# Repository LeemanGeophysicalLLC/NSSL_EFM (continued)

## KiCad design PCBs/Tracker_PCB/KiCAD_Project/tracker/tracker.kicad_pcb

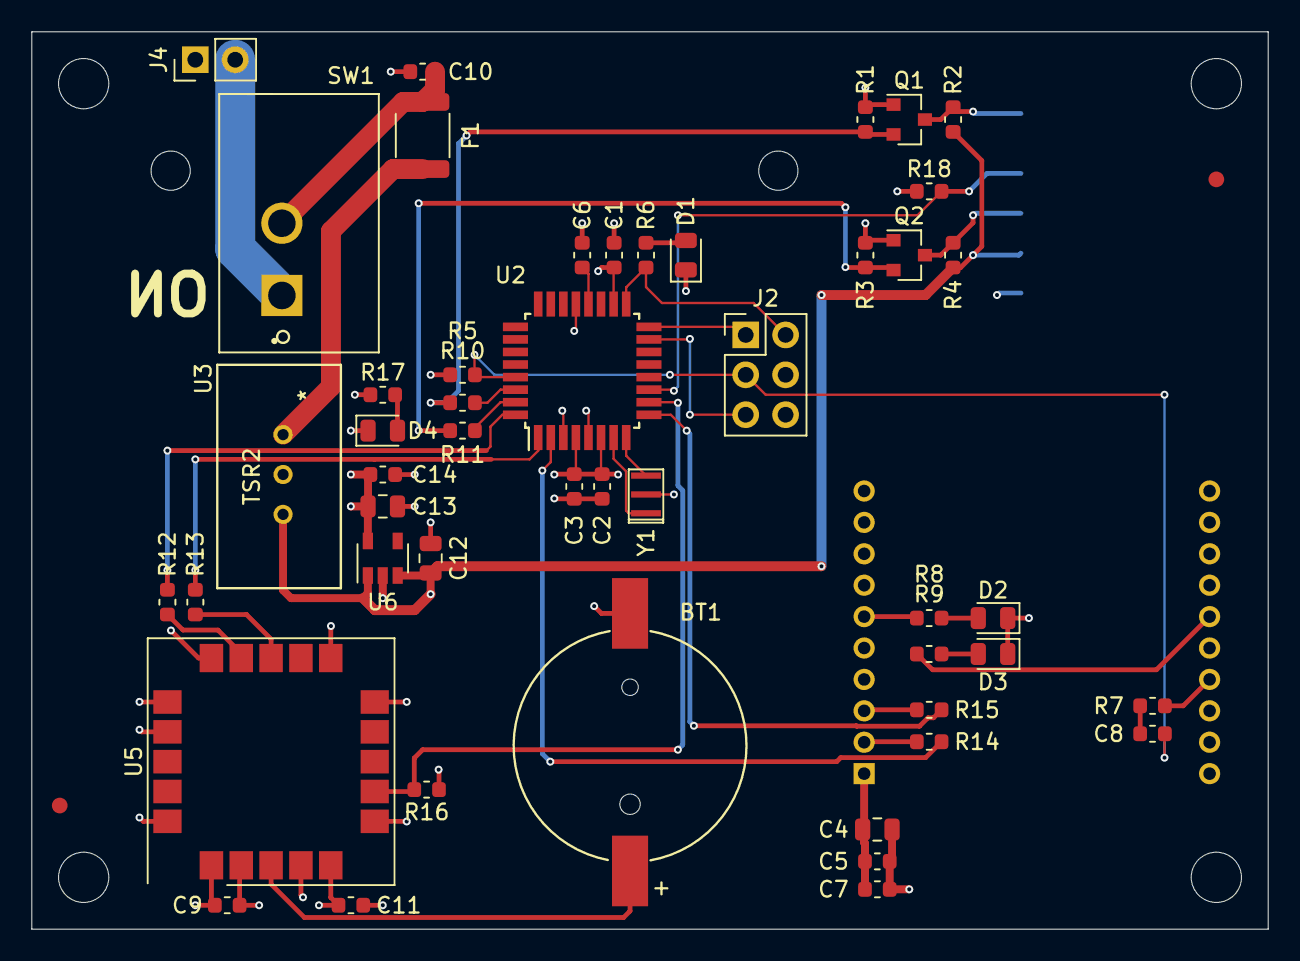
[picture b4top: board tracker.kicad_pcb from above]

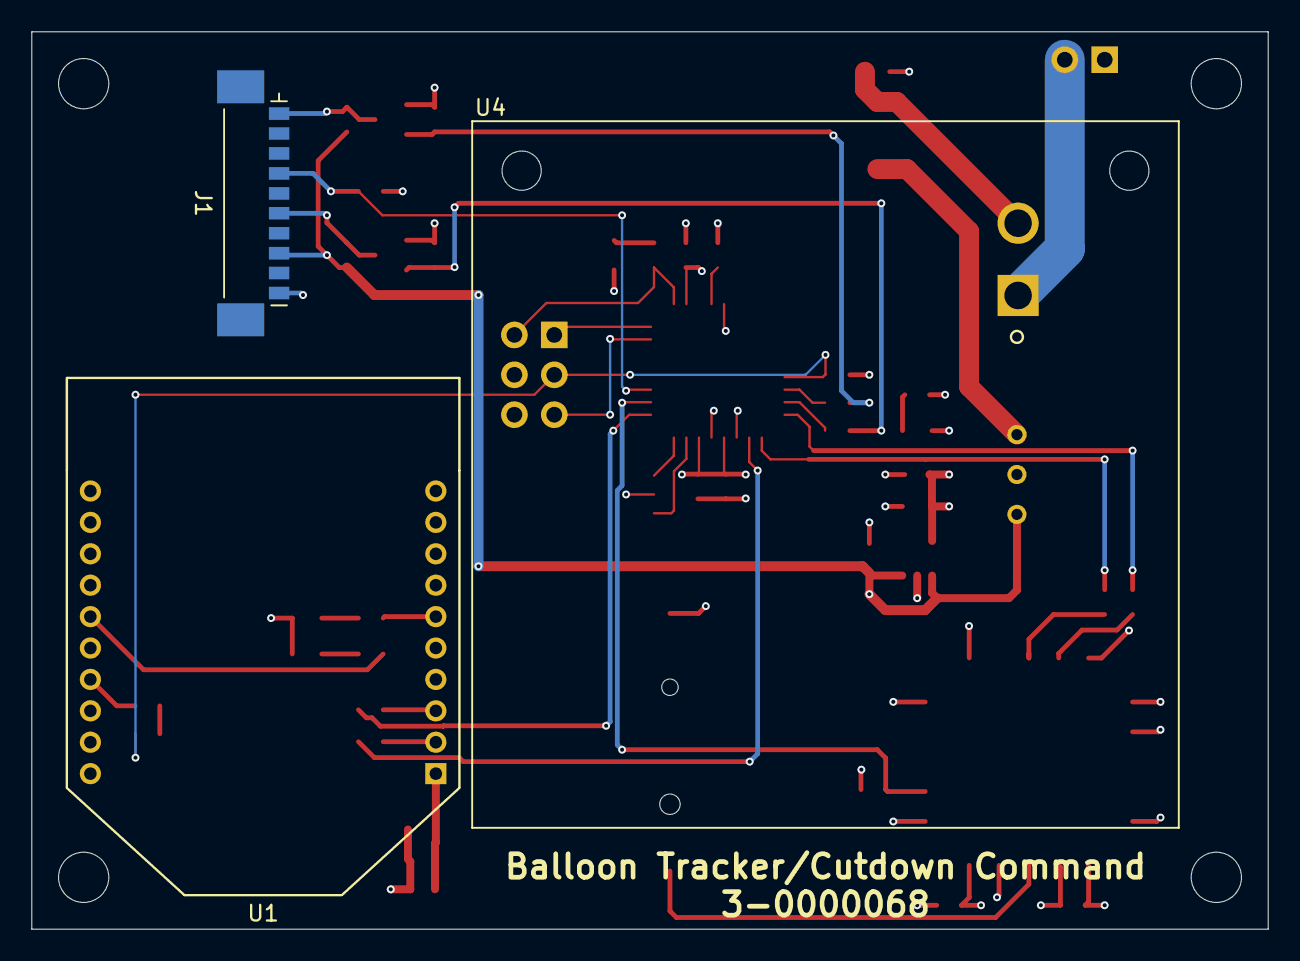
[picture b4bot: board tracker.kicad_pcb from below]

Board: 4 copper layers, 78.7 x 57.2 mm, 58 parts (3 on the bottom side), 38 nets.

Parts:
BT1: CR1220; S8411-45R
C1, C2, C3, C6, C7, C8, C9, C10, C11, C14: 1-0000007
C4, C12, C13: 1-0000075
C5: 1-0000018
D1, D2: Blue; LED_0805_2012Metric
D3: Yellow; LED_0805_2012Metric
D4: Green; LED_0805_2012Metric
F1: Polyfuse; Fuse_1812_4532Metric
FID1, FID2: Fiducial; Fiducial_1mm_Mask2mm
H1, H2, H3, H4: MountingHole; MountingHole_3.2mm_M3_DIN965
J1: RockBlock9603; picoblade
J2: ICSP; PinHeader_2x03_P2.54mm_Vertical
J4: Battery; PinHeader_1x02_P2.54mm_Vertical
PCB1: barepcb; BarePCB
Q1, Q2: BSS138; SOT-23
R1, R2, R3, R4: 1-0000013
R5, R16, R18: 1-0000010
R6, R8, R9, R17: 1-0000008
R7, R10, R11, R12, R13, R14, R15: 1-0000006
SW1: SW_SPST; SW_GF-123-0054
U1: XBee
U2: ATmega328P-AU; TQFP-32_7x7mm_P0.8mm
U3: TSR2; TSR 2-2450
U4: RockBlockMechanical; RockBlock_Mechanical
U5: ublox_SAM-M8Q
U6: MIC5219-3.3YM5; SOT-23-5
Y1: 16MHz; Resonator

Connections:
+3V3: C1.1, C2.1, C3.1, C4.1, C5.1, C7.1, C9.1, C11.1, C13.1, C14.1, J2.6, Q1.1, Q2.1, R1.1, R3.1, R5.1, R16.1, R17.1, R18.1, U1.1, U2.4, U2.6, U2.18, U5.2, U5.17, U6.5
GPS_PPS: R16.2, U2.10, U5.7
GPS_RX: R12.1, U5.14
GPS_TX: R13.1, U5.13
MISO: J2.1, U2.16
MOSI: J2.5, U2.15
unnamed: BT1.1, U5.3
unnamed: C6.1, U2.20
unnamed: C8.2, R7.1
unnamed: C10.1, F1.2, SW1.2
unnamed: D1.2, R6.2
unnamed: D2.2, R8.2
unnamed: D3.2, R9.2
unnamed: D4.2, R17.2
unnamed: F1.1, U3.1
unnamed: J4.2, SW1.1
unnamed: R7.2, U1.17
unnamed: R8.1, U1.6
unnamed: R9.1, U1.15
unnamed: R10.2, U2.30
unnamed: R11.2, U2.31
unnamed: R12.2, U2.32
unnamed: R13.2, U2.1
unnamed: R14.2, U2.2
unnamed: R15.2, U2.9
unnamed: U2.7, Y1.1
unnamed: U2.8, Y1.3
RB_5V: C12.1, J1.8, R2.1, R4.1, U3.3, U6.1, U6.3
RB_GND: BT1.2, C1.2, C2.2, C3.2, C4.2, C5.2, C6.2, C7.2, C9.2, C10.2, C11.2, C12.2, C13.2, C14.2, D1.1, D2.1, D3.1, D4.1, J1.10, J2.4, J4.1, U1.10, U2.3, U2.5, U2.21, U3.2, U5.1, U5.4, U5.5, U5.6, U5.10, U5.11, U5.15, U5.16, U5.20, U6.2, Y1.2
RB_NetAv: J1.4, R18.2, U2.11
RB_RXI: J1.6, Q2.3, R4.2
RB_RXI_3V3: Q2.2, R3.2, R11.1
RB_TXO: J1.1, Q1.3, R2.2
RB_TXO_3V3: Q1.2, R1.2, R10.1
RESET: C8.1, J2.3, R5.2, U2.29
SCK: J2.2, R6.1, U2.17
XBee_from_Uc: R15.1, U1.3
XBee_to_Uc: R14.1, U1.2

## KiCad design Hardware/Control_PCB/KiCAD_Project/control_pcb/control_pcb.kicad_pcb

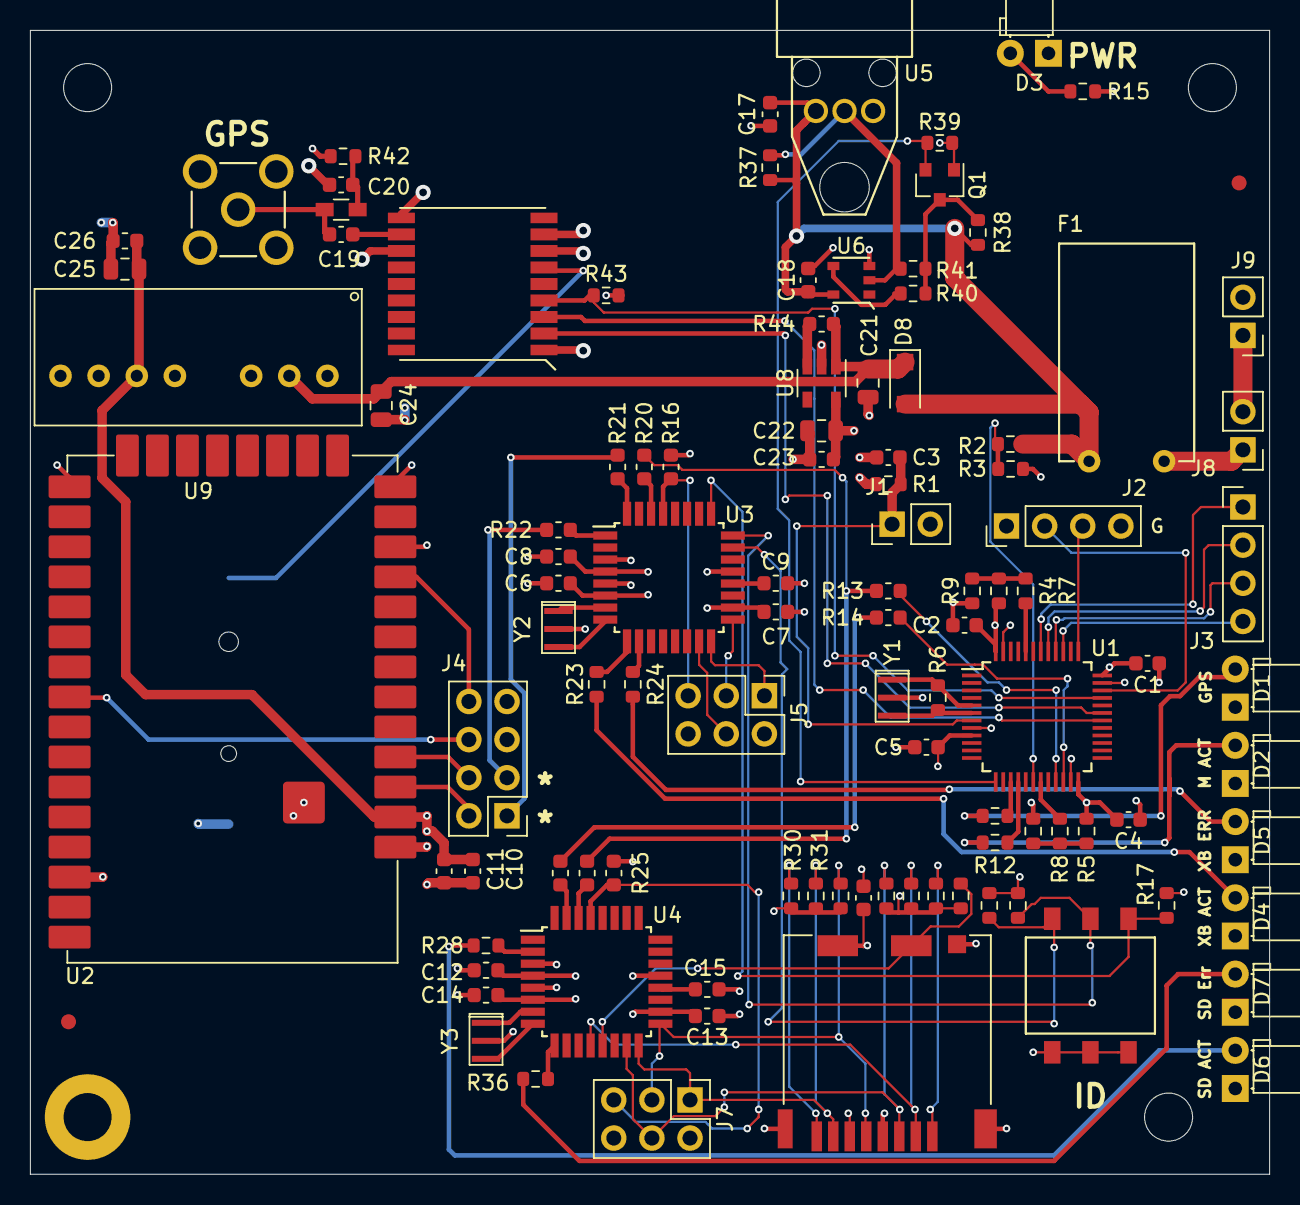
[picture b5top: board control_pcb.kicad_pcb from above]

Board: 4 copper layers, 82.6 x 76.2 mm, 112 parts (1 on the bottom side), 82 nets.

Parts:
AE1: Antenna_Shield; SMA
BT1: CR1220; S8411-45R
C1, C2, C4, C5, C16, C17, C18: 0.1u; C_0603_1608Metric
C3, C11: 1u; C_0603_1608Metric
C6, C7, C8, C9, C12, C13, C14, C15: 1-0000007
C10: 10u; C_0603_1608Metric
C19: 47pF; C_0603_1608Metric
C20: 10nF; C_0603_1608Metric
C21, C22, C24, C25: 1-0000075
C23, C26: 1-0000018
D1: GPS; LED_D3.0mm_Horizontal_O1.27mm_Z2.0mm_Clear
D2: ACT; LED_D3.0mm_Horizontal_O1.27mm_Z2.0mm_Clear
D3: Power; LED_D3.0mm_Horizontal_O1.27mm_Z2.0mm_Clear
D4, D6: Activity; LED_D3.0mm_Horizontal_O1.27mm_Z2.0mm_Clear
D5, D7: Error; LED_D3.0mm_Horizontal_O1.27mm_Z2.0mm_Clear
D8: D_Schottky; D_SOD-123F
F1: Polyfuse; RGEF250
FID1, FID2: Fiducial; Fiducial_1mm_Mask2mm
H1, H2, H3: MountingHole; MountingHole_3.2mm_M3_ISO7380
H4: MountingHole; MountingHole_3.2mm_M3_ISO7380_Pad
J1: Conn_01x02; Pin_Header_Straight_1x02_Pitch2.54mm
J2: ISP; Pin_Header_Straight_1x04_Pitch2.54mm
J3: Spare; Pin_Header_Straight_1x04_Pitch2.54mm
J4: XBee ISP; PinHeader_2x04_P2.54mm_Vertical
J5: XBee_uC_ISP; PinHeader_2x03_P2.54mm_Vertical
J6: Micro_SD_Card_Det; HRS_DM3CS-SF
J7: SD_uC_ISP; PinHeader_2x03_P2.54mm_Vertical
J8: External Switch; PinHeader_1x02_P2.54mm_Vertical
J9: Battery; PinHeader_1x02_P2.54mm_Vertical
L1: 27nH; R_0603_HandSoldering
PCB1: barepcb
Q1: BSS138; SOT-23
R1, R3, R17, R18, R19, R37, R38, R39: 10k; R_0603_1608Metric
R2: 18k; R_0603_1608Metric
R4, R5, R32, R41, R43: NP; R_0603_1608Metric
R6: 1M; R_0603_1608Metric
R7, R8, R29, R30, R31, R33, R34, R35: 100k; R_0603_1608Metric
R9, R10, R40: 0R0; R_0603_1608Metric
R11, R12, R15, R23, R24, R28, R36: 150; R_0603_1608Metric
R13, R14, R20, R21, R22, R26, R27: 1-0000006
R16, R25: 1-0000010
R42: 1-0000678; R_0603_1608Metric
R44: 1-0000174
SW1: ID Select; KAE03TGGR
U1: STM32F103CBT6; LQFP-48_7x7mm_Pitch0.5mm
U2: XTend
U3, U4: ATmega328P-AU; TQFP-32_7x7mm_P0.8mm
U5: IF-D96F
U6: TC4S584F; SOT753
U7: MAX-M8C; XCVR_MAX-M8C-0-10
U8: SPX3819M5-L-3-3; SOT-23-5
U9: 1-0000946
Y1, Y2, Y3: 8MHz; Resonator

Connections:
3V3_XBEE: C10.1, C11.1, C25.1, C26.1, U2.2, U9.6
+3V3: C1.2, C2.2, C4.2, C5.2, C6.1, C7.1, C8.1, C12.1, C13.1, C14.1, C16.2, C22.1, C23.1, J2.1, J5.2, J6.4, J7.2, Q1.1, R1.1, R4.2, R5.2, R15.2, R16.1, R17.1, R18.1, R19.1, R25.1, R29.1, R30.1, R31.1, R32.1, R33.1, R34.1, R35.1, R39.1, R42.1, R43.2, U1.9, U1.24, U1.36, U1.48, U3.4, U3.6, U3.18, U4.4, U4.6, U4.18, U7.7, U7.8, U8.5
+BATT: C17.1, C18.1, D8.2, F1.1, R2.1, R37.1, R38.1, U5.3, U6.5
/Boot0: R7.2, U1.44
/Boot1: R8.2, U1.19
/Reset: C3.1, J1.1, R1.2, U1.7
/SD/SD_uC_CD: J6.9, R29.2, U4.13
/SD/SD_uC_CS: J6.2, R34.2, U4.12
/SD/SD_uC_MISO: J6.7, J7.1, R31.2, U4.16
/SD/SD_uC_MOSI: J6.3, J7.4, R33.2, U4.15
/SD/SD_uC_RESET: J7.5, R25.2, U4.29
/SD/SD_uC_SCK: J6.5, J7.3, R32.2, U4.17
/SWCLK: J2.3, U1.37
/SWDIO: J2.2, U1.34
/VBat_Sense: R2.2, R3.1, U1.18
/radio/XBEE_uC_MISO: J5.1, U3.16
/radio/XBEE_uC_MOSI: J5.4, U3.15
/radio/XBEE_uC_RESET: J5.5, R16.2, U3.29
/radio/XBEE_uC_SCK: J5.3, U3.17
Fiber_Serial_In: Q1.2, R39.2, U1.13
GND: AE1.2, BT1.2, C1.1, C2.1, C3.2, C4.1, C5.1, C6.2, C7.2, C8.2, C9.2, C10.2, C11.2, C12.2, C13.2, C14.2, C15.2, C16.1, C17.2, C18.2, C20.1, C21.2, C22.2, C23.2, C24.2, C25.2, C26.2, D1.1, D2.1, D3.1, D4.1, D5.1, D6.1, D7.1, H4.1, J1.2, J2.4, J5.6, J6.6, J6.S1, J6.S2, J6.S3, J6.S5, J7.6, J9.2, R3.2, R9.1, R10.1, SW1.1, SW1.2, SW1.3, U1.8, U1.23, U1.35, U1.47, U2.1, U2.11, U2.13, U2.22, U2.35, U2.38, U3.3, U3.5, U3.21, U4.3, U4.5, U4.21, U5.1, U6.3, U7.1, U7.10, U7.12, U8.2, U9.1, U9.7, Y1.2, Y2.2, Y3.2
GPS_PPS: R43.1, U1.33, U7.4
unnamed: AE1.1, C19.1, L1.1
unnamed: BT1.1, U7.6
unnamed: C9.1, U3.20
unnamed: C15.1, U4.20
unnamed: C19.2, U7.11
unnamed: C20.2, L1.2, R42.2
unnamed: C21.1, C24.1, D8.1, R44.1, U8.1, U9.2
unnamed: D1.2, R11.1
unnamed: D2.2, R12.1
unnamed: D3.2, R15.1
unnamed: D4.2, R23.1
unnamed: D5.2, R24.1
unnamed: D6.2, R28.1
unnamed: D7.2, R36.1
unnamed: F1.2, J8.1
unnamed: J3.1, U1.42
unnamed: J3.2, U1.41
unnamed: J3.3, U1.40
unnamed: J3.4, U1.39
unnamed: J4.2, U2.3
unnamed: J4.4, U2.4
unnamed: J4.6, U2.29
unnamed: J4.8, U2.10
unnamed: J6.1, R35.2
unnamed: J6.8, R30.2
unnamed: J8.2, J9.1
unnamed: Q1.3, R38.2, R40.1, R41.1
unnamed: R4.1, R7.1, R9.2
unnamed: R6.1, U1.5, Y1.1
unnamed: R6.2, U1.6, Y1.3
unnamed: R5.1, R8.1, R10.2
unnamed: R11.2, U1.15
unnamed: R12.2, U1.16
unnamed: R13.1, U1.21
unnamed: R14.1, U1.22
unnamed: R17.2, SW1.4, U3.25
unnamed: R18.2, SW1.5, U3.24
unnamed: R19.2, SW1.6, U3.23
unnamed: R20.2, U3.30
unnamed: R21.2, U3.32
unnamed: R22.2, U3.1
unnamed: R23.2, U3.9
unnamed: R24.2, U3.10
unnamed: R26.2, U4.30
unnamed: R27.2, U4.31
unnamed: R28.2, U4.2
unnamed: R36.2, U4.9
unnamed: R37.2, R41.2, U5.2, U6.2
unnamed: R40.2, U6.4
unnamed: R44.2, U8.3
unnamed: U3.7, Y2.1
unnamed: U3.8, Y2.3
unnamed: U4.7, Y3.1
unnamed: U4.8, Y3.3
RX_FROM_RADIO: J4.1, R21.1
RX_FROM_STM: R13.2, R20.1, R26.1
RX_from_GPS: U1.31, U7.2
TX_TO_RADIO: J4.3, R22.1
TX_TO_STM: R14.2, R27.1
TX_to_GPS: U1.30, U7.3

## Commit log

2022-03-25 R42: 1-460 -> 1-678
2022-05-06 Cuttdown Users Guide
2022-08-08 Updates to run at 40Hz and fix IMU reading scale. Tested with Eric B. on August 6th with demo unit.
2022-08-08 Update comments
2022-10-11 Allow external or remote cutdown regardless of if the flight is terminated
2022-10-11 Move cutdown to a product repo as it is not EFM specific
2022-11-29 Update GERBERS to match production
2022-11-29 Restructure to add mechanical files as well
2022-11-29 Add PDFs of mechanical drawings
2022-11-29 Add readme and mechanical files
2022-11-29 Cleanup README spacing.
2022-11-29 Fix CR123 PCBA image
2022-11-29 Remove unused CR2 PCBA
2022-11-29 Move KiCAD project files up a level
2024-03-22 Added Orientation Paddle Project
2024-03-22 Updated Ori. Paddle Schematic with Final Revisions
2024-03-22 Orientation Paddle Initial PCB Layout
2024-03-26 Initial Digtal Rotating PCB Layout
2024-03-26 Initial Motor Control PCB Layout
2024-03-28 Make production files for new motor PCB
2024-03-28 Update with some fixes
2024-03-28 Rearrange and remove old files
2024-03-28 Minor fixups
2024-03-28 Orientation Paddle Revisions: Board resize to nice numbers Fixed Footprint/Symbols causing ERC Errors Fixed remaining ERC Errors (Schematic and PCB)
2024-03-28 Add digital PCB reorganized
2024-03-28 Digital PCB Revisions: Fixed ERC Footprint/Symbol Errors Fixed Remaining ERC Errors Relocated U7 to bottom of PCB
2024-03-28 Fixed Motor PCB ERC Issues and Copper to Edge Clearence
2024-03-28 Fixed Orientation Paddle ERC Issues and Copper to Edge Clearence
2024-04-03 Fixed Orientation Paddle to Have only 2 layer instead of 4
2024-04-30 Change telemetry interval to 10 mintues after 90 minutes of operation.
